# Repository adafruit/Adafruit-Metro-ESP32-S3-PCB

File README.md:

## Adafruit Metro ESP32-S3 with 16 MB Flash 8MB PSRAM PCB

<a href="http://www.adafruit.com/products/5500"><br/>
Click here to purchase one from the Adafruit shop</a>

PCB files for the Adafruit Metro ESP32-S3 with 16 MB Flash 8MB PSRAM. 

Format is EagleCAD schematic and board layout
* https://www.adafruit.com/product/5500

### Description

What's Metro-shaped and has an ESP32-S3 WiFi module? What has a STEMMA QT connector for I2C devices and a Lipoly charger circuit? What has your favorite Espressif WiFi microcontroller and lots of memory for your next IoT project?

That's right - it's the new Adafruit Metro ESP32-S3! With native USB and a load of PSRAM, this board is perfect for use with CircuitPython or Arduino to add low-cost WiFi while retaining shield compatibility.

The ESP32-S3 is a highly-integrated, low-power, 2.4 GHz Wi-Fi/BLE System-on-Chip (SoC) solution that has built-in native USB as well as some other interesting new technologies like Time of Flight distance measurements and AI acceleration. With its state-of-the-art power and RF performance, this SoC is an ideal choice for a wide variety of application scenarios relating to the Internet of Things (IoT), wearable electronics, and smart homes.

The Metro ESP32-S3 has a dual-core 240 MHz chip, so it is comparable to ESP32's dual-core. However, there is no Bluetooth Classic support, only Bluetooth LE. This chip is a great step up from the earlier ESP32-S2! This ESP32-S3 mini-module we are using on the Metro comes with massive 16 MB flash and 8 MB PSRAM, as well as lots of 512KB of SRAM so it's perfect for use with CircuitPython support or any time massive buffers are needed: for fast memory access use SRAM, for slower-but-roomier access use PSRAM. It's also great for use in ESP-IDF or with Arduino support.

Features:

* ESP32-S3 Dual Core 240MHz Tensilica processor - the next generation of ESP32-Sx, with native USB so it can act like a keyboard/mouse, MIDI device, disk drive, etc!
* Mini module has FCC/CE certification and comes with 16 MByte of Flash, 8 MByte PSRAM
* Power options - USB type C or Lipoly battery
* Built-in battery charging when powered over USB-C
* LiPoly battery monitor - MAX17048 chip actively monitors your battery for voltage and state of charge / percentage reporting over I2C
* Reset and DFU (BOOT0) buttons to get into the ROM bootloader (which is a USB serial port so you don't need a separate cable!)
* JTAG 2x5 Header for more intense debugging
* Serial debug output pins (optional, for checking the hardware serial debug console)
* STEMMA QT connector for I2C devices, with switchable power, so you can go into low power mode.
* On/Charge/User LEDs + status NeoPixel with pin-controlled power for low power usage
* Low Power friendly! In deep sleep mode we can get down to ~100uA of current draw from the Lipoly connection. Quiescent current is from the power regulator, ESP32-S3 chip, and Lipoly monitor. Turn off the NeoPixel and external I2C power for the lowest quiescent current draw.
* Works with ESP-IDF, Arduino or CircuitPython 

<b>As of Nov 8, 2023</b> - We've fixed this hardware to be revision B which has changed the NeoPixel pin and the SPI/SD card pins to no longer use the same pins as the octal PSRAM. Which means that the hardware now works correctly when PSRAM is activated! If you have a rev A hardware board, contact support to get a replacement rev B.

### License

Adafruit invests time and resources providing this open source design, please support Adafruit and open-source hardware by purchasing products from [Adafruit](https://www.adafruit.com)!

Designed by Limor Fried/Ladyada for Adafruit Industries.

Creative Commons Attribution/Share-Alike, all text above must be included in any redistribution. 
See license.txt for additional details.

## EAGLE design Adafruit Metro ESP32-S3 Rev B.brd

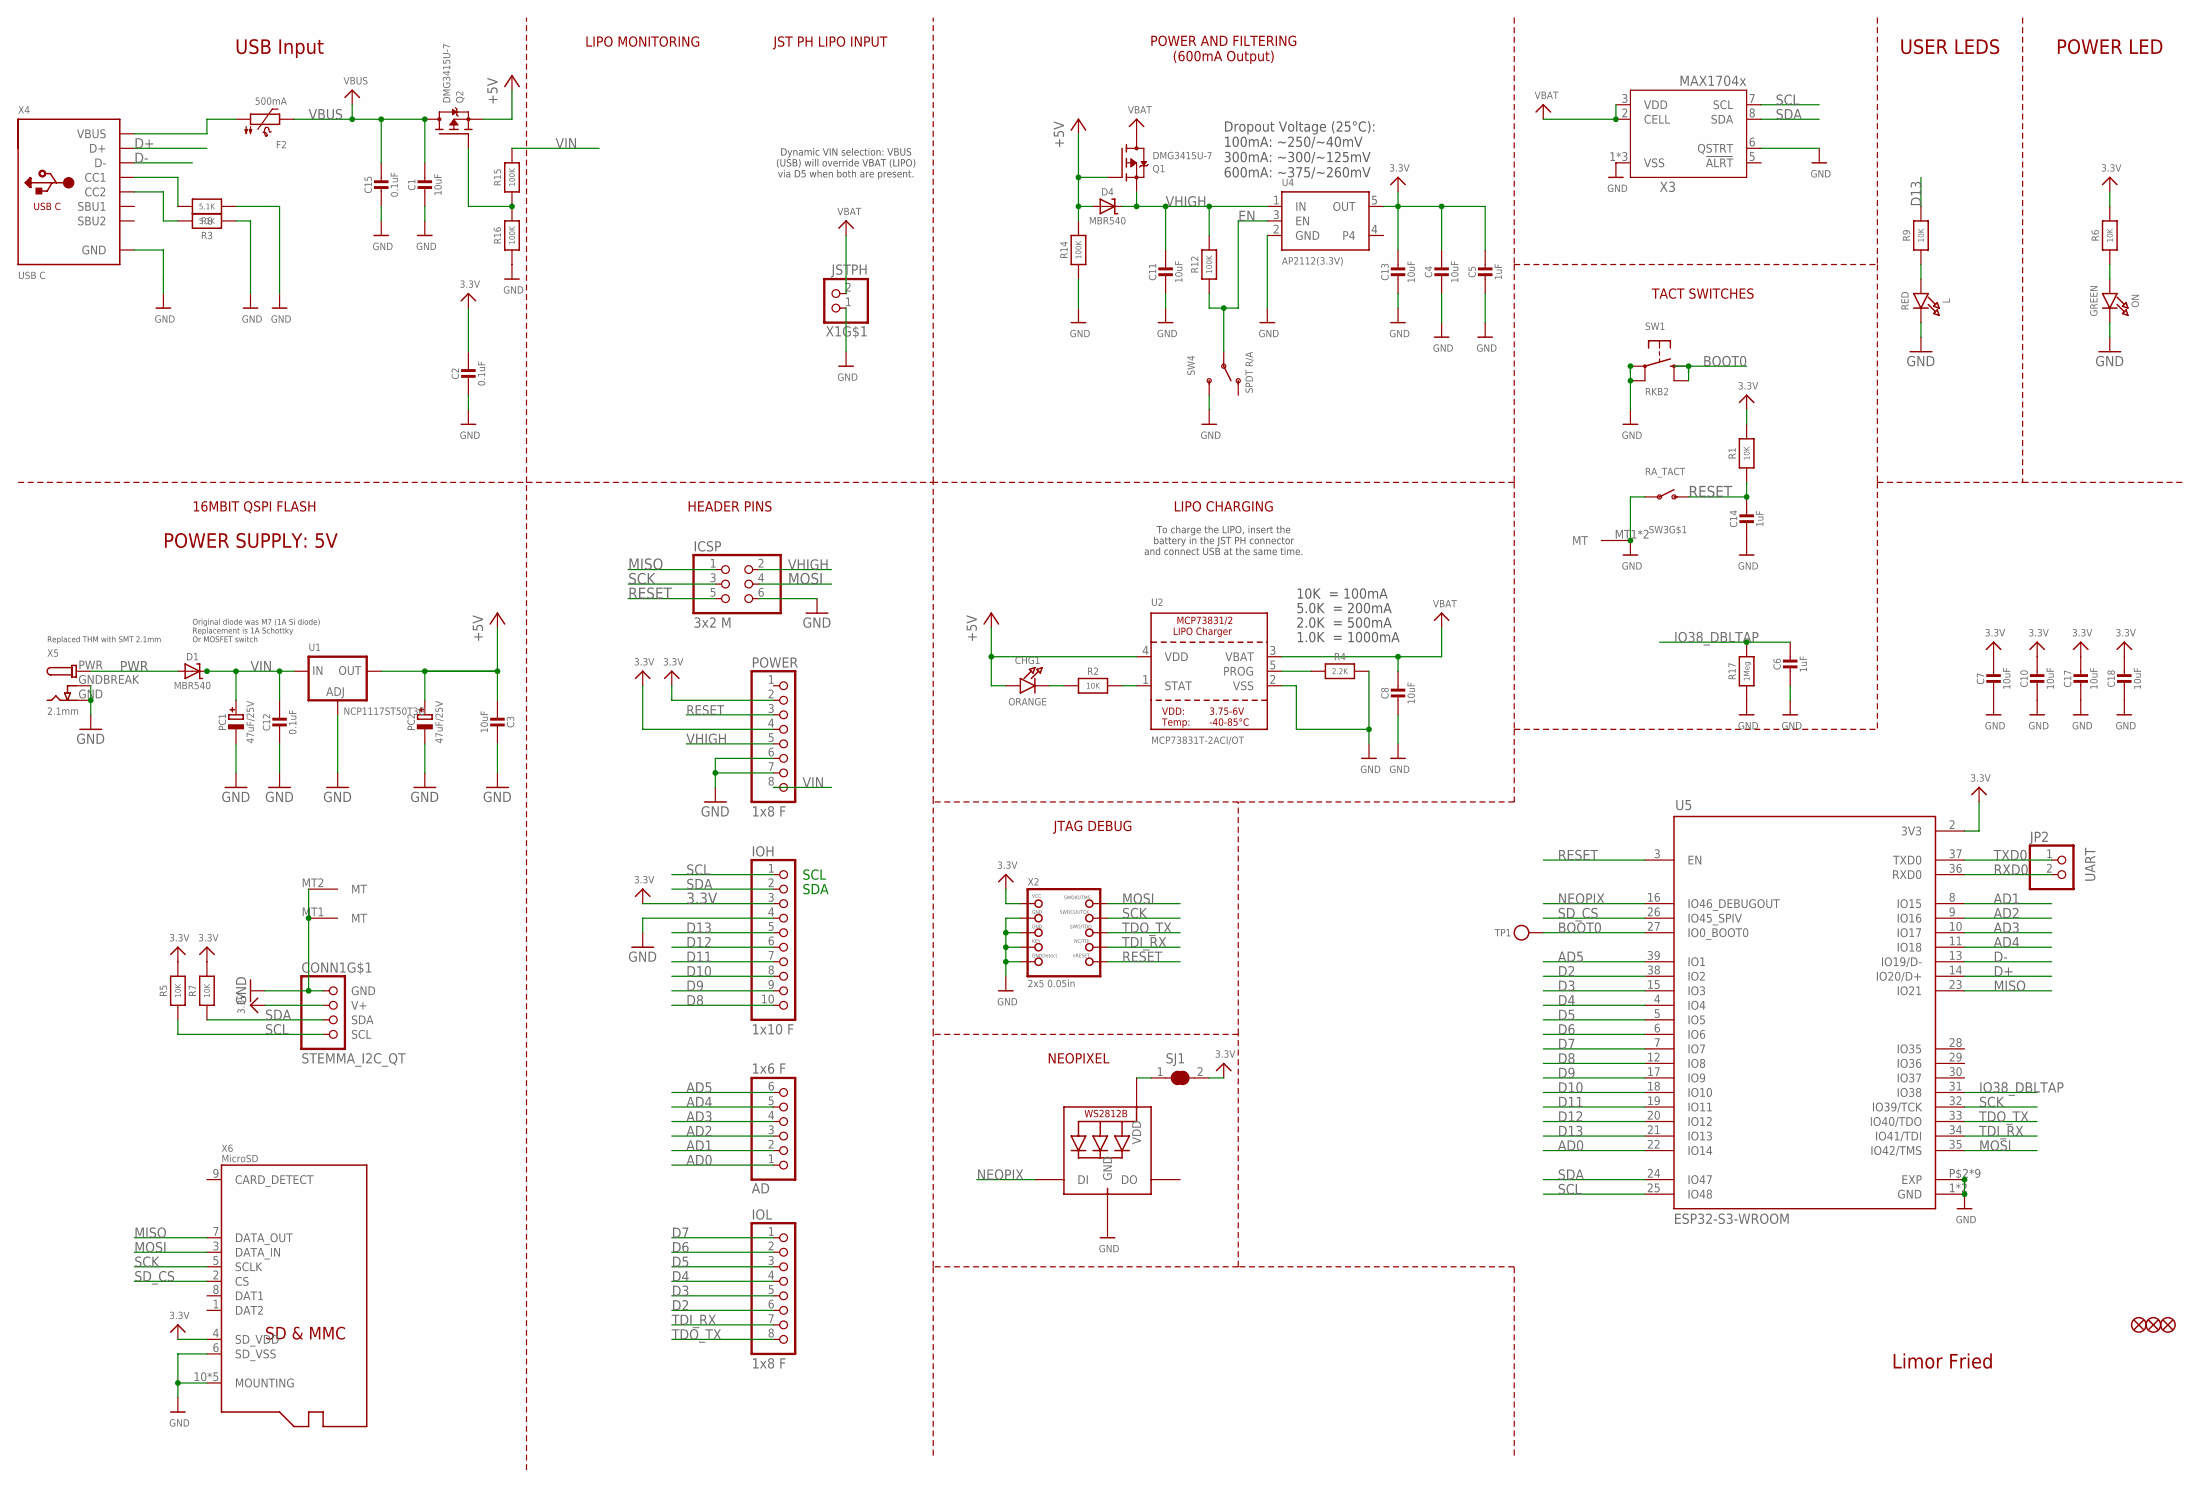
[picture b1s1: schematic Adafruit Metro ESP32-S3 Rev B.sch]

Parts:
AD: 1x6 F; 1X06_OVALWAVE
C1, C3, C4, C7, C8, C10, C11, C13, C17, C18: 10uF; 0805-NO
C2, C12, C15: 0.1uF; 0603-NO
C5, C6, C14: 1uF; 0603-NO
CHG1: ORANGE; CHIPLED_0603_NOOUTLINE
CONN1: STEMMA_I2C_QT; JST_SH4
D1, D4: MBR540; SOD-123
F2: 500mA; 0805-NO
FD1, FD2, FD3: FIDUCIAL_1MM
ICSP: 3x2 M; 2X03_ROUND_70MIL
IOH: 1x10 F; 1X10_OVALWAVE
IOL: 1x8 F; 1X08_OVALWAVE
JP2: UART; 1X02_ROUND
L: RED; CHIPLED_0603_NOOUTLINE
LED1: WS2812B_3535FULL; LED3535_FULLPADS
ON: GREEN; CHIPLED_0603_NOOUTLINE
PC1, PC2: 47uF/25V; PANASONIC_D
POWER: 1x8 F; 1X08_OVALWAVE
Q1, Q2: DMG3415U-7; SOT23-R
R1, R2, R5, R6, R7, R9: 10K; 0603-NO
R3, R8: 5.1K; 0603-NO
R4: 2.2K; 0603-NO
R12, R14, R15, R16: 100K; 0603-NO
R17: 1Meg; 0603-NO
SJ1: SOLDERJUMPER_CLOSED; SOLDERJUMPER_CLOSEDWIRE
SW1: RKB2; BTN_RKB2_4.6X2.8
SW3: RA_TACT; SPST_TACTILE_RA
SW4: SPDT R/A; SPDT_SMT_SSSS811101
TP1: TESTPOINTROUND1.5MMNO; TESTPOINT_ROUND_1.5MM_NO
U1: NCP1117ST50T3G; SOT223-R
U2: MCP73831T-2ACI/OT; SOT23-5
U4: AP2112(3.3V); SOT23-5; JLC_ROTATION 0
U5: ESP32-S3-WROOM; S3-WROOM32
X1: JSTPH; JSTPH2_BATT
X2: 2x5 0.05in; 2X05_1.27MM_BOX_POSTS
X3: MAX17048/T; TDFN8_2X2MM
X4: USB C; USB_C_CUSB31-CFM2AX-01-X
X5: 2.1mm; DCJACK_2MM_PTH
X6: MicroSD; MOLEX_104031-0811

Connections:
3.3V: C2.1, C4.1, C5.1, C7.1, C10.1, C13.1, C17.1, C18.1, CONN1.2 (V+), IOH.3, POWER.2, POWER.4, R1.2, R5.2, R6.2, R7.2, SJ1.2, U4.5 (OUT), U5.2 (3V3), X2.1 (VCC), X6.4 (SD_VDD)
+5V: C3.2, CHG1.A, D4.A, PC2.+, Q1.1 (G), Q2.2 (S), R14.2, U1.2 (OUT), U1.4 (OUT), U2.4 (VDD)
AD0: AD.1, U5.22 (IO14)
AD1: AD.2, U5.8 (IO15)
AD2: AD.3, U5.9 (IO16)
AD3: AD.4, U5.10 (IO17)
AD4: AD.5, U5.11 (IO18)
AD5: AD.6, U5.39 (IO1)
BOOT0: SW1.B (S), SW1.B' (S1), TP1.P$1, U5.27 (IO0_BOOT0)
D2: IOL.6, U5.38 (IO2)
D3: IOL.5, U5.15 (IO3)
D4: IOL.4, U5.4 (IO4)
D5: IOL.3, U5.5 (IO5)
D6: IOL.2, U5.6 (IO6)
D7: IOL.1, U5.7 (IO7)
D8: IOH.10, U5.12 (IO8)
D9: IOH.9, U5.17 (IO9)
D10: IOH.8, U5.18 (IO10)
D11: IOH.7, U5.19 (IO11)
D12: IOH.6, U5.20 (IO12)
D13: IOH.5, R9.2, U5.21 (IO13)
D+: U5.14 (IO20/D+), X4.A6 (D+), X4.B6 (D+)
D-: U5.13 (IO19/D-), X4.A7 (D-), X4.B7 (D-)
EN: R12.1, SW4.B, U4.3 (EN)
GND: C1.2, C2.2, C3.1, C4.2, C5.2, C6.2, C7.2, C8.2, C10.2, C11.2, C12.2, C13.2, C14.2, C15.2, C17.2, C18.2, CONN1.1 (GND), CONN1.MT1 (MT), CONN1.MT2 (MT), ICSP.6, IOH.4, L.C, LED1.4 (GND), ON.C, PC1.-, PC2.-, POWER.6, POWER.7, R3.1, R4.2, R8.1, R14.1, R16.1, R17.1, SW1.A, SW1.A' (P1), SW3.1, SW3.MT1 (MT), SW3.MT2 (MT), SW4.C (S), U1.1 (ADJ), U2.2 (VSS), U4.2 (GND), U5.1 (GND), U5.40 (GND), U5.P$2 (EXP), U5.P$3 (EXP), U5.P$4 (EXP), U5.P$5 (EXP), U5.P$6 (EXP), U5.P$7 (EXP), U5.P$8 (EXP), U5.P$9 (EXP), U5.P$10 (EXP), X1.1, X2.3 (GND), X2.5 (GND), X2.7 (KEY), X2.9 (GNDDETECT), X3.1 (VSS), X3.4 (VSS), X3.6 (QSTRT), X3.THERMAL (VSS), X4.A1B12 (GND), X4.B1A12 (GND), X5.GND, X5.GNDBREAK, X6.6 (SD_VSS), X6.10 (MOUNTING), X6.G1 (MOUNTING), X6.G2 (MOUNTING), X6.G3 (MOUNTING), X6.G4 (MOUNTING)
IO38_DBLTAP: C6.1, R17.2, U5.31 (IO38)
MISO: ICSP.1, U5.23 (IO21), X6.7 (DATA_OUT)
MOSI: ICSP.4, U5.35 (IO42/TMS), X2.2 (SWDIO), X6.3 (DATA_IN)
unnamed: L.A, R9.1
unnamed: Q2.1 (G), R15.1, R16.2
unnamed: ON.A, R6.1
unnamed: CHG1.C, R2.1
unnamed: LED1.2 (VDD), SJ1.1
unnamed: R2.2, U2.1 (STAT)
unnamed: R8.2, X4.A5 (CC1)
unnamed: R3.2, X4.B5 (CC2)
unnamed: R4.1, U2.5 (PROG)
unnamed: F2.1, X4.A4B9 (VBUS), X4.B4A9 (VBUS)
NEOPIX: LED1.1 (DI), U5.16 (IO46_DEBUGOUT)
PWR: D1.A, X5.PWR
RESET: C14.1, ICSP.5, POWER.3, R1.1, SW3.2 (S), U5.3 (EN), X2.10 (NRESET)
RXD0: JP2.2, U5.36 (RXD0)
SCK: ICSP.3, U5.32 (IO39/TCK), X2.4 (SWDCLK), X6.5 (SCLK)
SCL: CONN1.4 (SCL), IOH.1, R5.1, U5.25 (IO48), X3.7 (SCL)
SDA: CONN1.3 (SDA), IOH.2, R7.1, U5.24 (IO47), X3.8 (SDA)
SD_CS: U5.26 (IO45_SPIV), X6.2 (CS)
TDI_RX: IOL.7, U5.34 (IO41/TDI), X2.8 (TDI)
TDO_TX: IOL.8, U5.33 (IO40/TDO), X2.6 (SWO)
TXD0: JP2.1, U5.37 (TXD0)
VBAT: C8.1, Q1.3 (D), U2.3 (VBAT), X1.2, X3.2 (CELL), X3.3 (VDD)
VBUS: C1.1, C15.1, F2.2, Q2.3 (D)
VHIGH: C11.1, D4.C, ICSP.2, POWER.5, Q1.2 (S), R12.2, U4.1 (IN)
VIN: C12.1, D1.C, PC1.+, POWER.8, R15.2, U1.3 (IN)

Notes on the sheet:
SDA
SCL
Limor Fried
USB Input
POWER LED
USER LEDS
10K = 100mA
5.0K = 200mA
2.0K = 500mA
1.0K = 1000mA
LIPO CHARGING
LIPO MONITORING
To charge the LIPO, insert the battery in the JST PH connector and connect USB at the same time.
POWER AND FILTERING (600mA Output)
JST PH LIPO INPUT
Dynamic VIN selection: VBUS (USB) will override VBAT (LIPO) via D5 when both are present.
Dropout Voltage (25°C): 100mA: ~250/~40mV 300mA: ~300/~125mV 600mA: ~375/~260mV
HEADER PINS
16MBIT QSPI FLASH
TACT SWITCHES
JTAG DEBUG
NEOPIXEL
Original diode was M7 (1A Si diode) Replacement is 1A Schottky Or MOSFET switch
Replaced THM with SMT 2.1mm
POWER SUPPLY: 5V

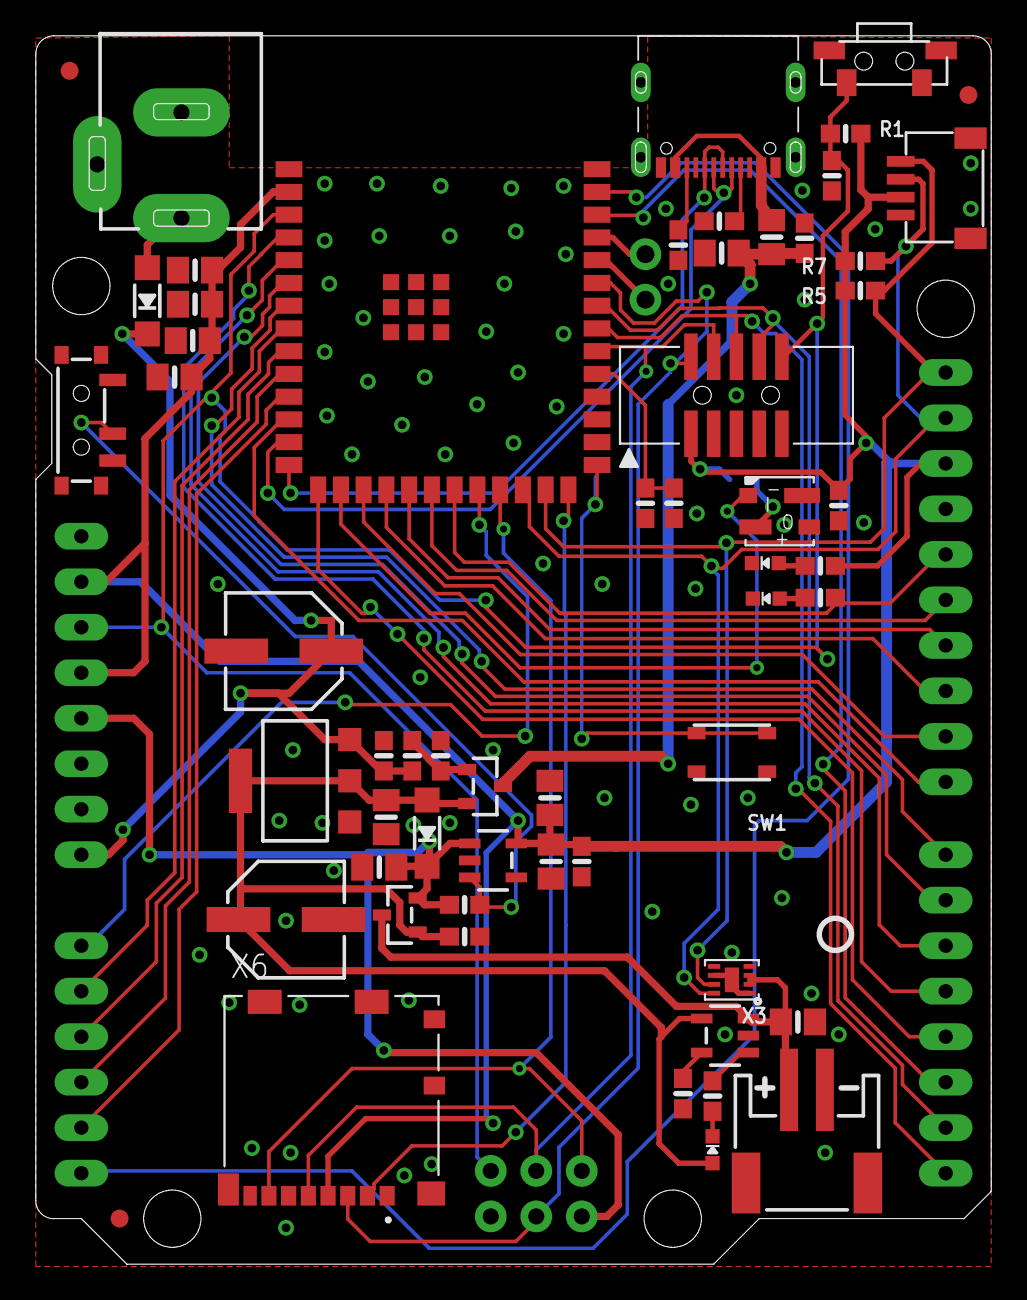
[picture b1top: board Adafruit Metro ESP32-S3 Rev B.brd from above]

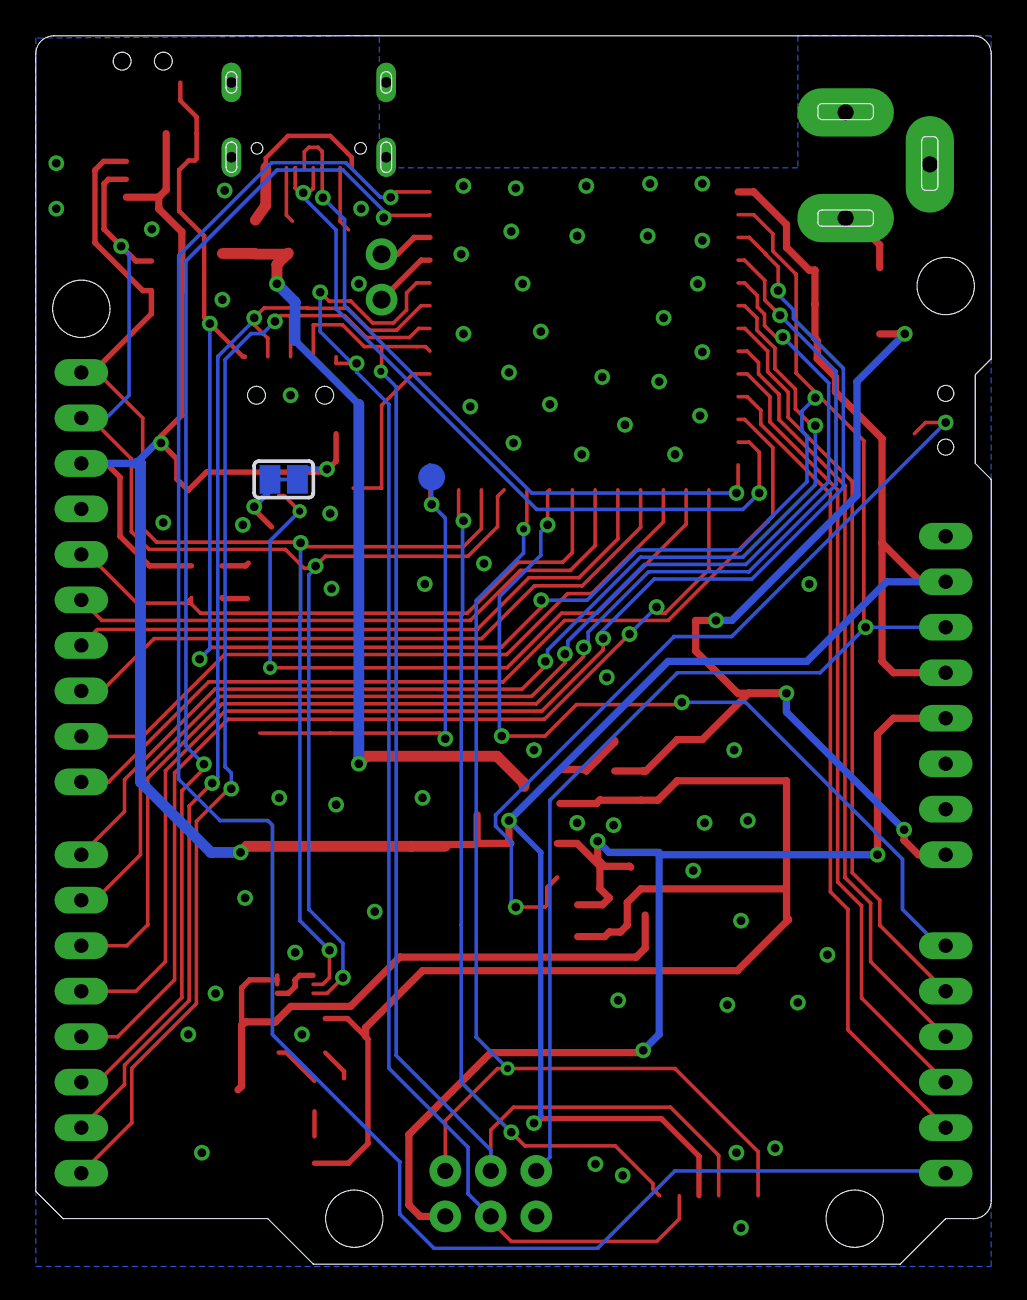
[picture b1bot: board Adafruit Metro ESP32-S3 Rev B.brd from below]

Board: 2 copper layers, 53.3 x 68.6 mm, 69 parts (3 on the bottom side), 53 nets.

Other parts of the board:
U$15: PCBFEAT-REV-040
U$52: METROS3_TOP
U$58: METROS3_BOT

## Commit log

2023-08-22 Add board files.
2023-08-24 Add factory reset file.
2023-08-24 Add factory reset UF2.
2023-11-09 update for rev B
2023-11-10 update prettypins
2023-11-10 update factory reset for rev b

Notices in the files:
parts and their libraries:
microbuilder: This work is placed in the public domain, and may be freely used for commercial and non-commercial work with the following conditions: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
